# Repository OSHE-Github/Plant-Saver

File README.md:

# Plant-Saver
## Project Description
Many new gardeners or horticulturists struggle to create a proper environment for plant growth. The Plant-Saver aims to simplify the process and provide proper recommendations for the user. Housed in a convenient form factor, the device will analyze local conditions including temperature, soil moisture, humidity, and lighting. This data is utilized to provide recommendations for compatible species or for improving the care of a specific nearby plant. A simple local UI and accompanying web application ensures this information can be accessed efficiently in an easily digestible format. Environmental data is displayed along with an indication of how it compares to ideal conditions. Displaying the raw data readings while expressing recommended changes in simple terms allows the user to have a better understanding of their plant’s environment and how to alter it for improved growth.

*Main product image*

## Repository Structure
Project information/resources from semester 1 can be found in the folder Plant_Saver_Spring_2025. The newest iteration of the project from semester 2 is located in Plant_Saver_Fall_2026. This includes the following files/directories:
1. `Code`: Contains the arduino project used to program the Plant-Saver.
2. `JHA`: A job hazard analysis performed for the project.
3. `Plant_Saver_Kicad`: The KiCad project used to design the Plant-Saver’s PCB. This is the original version of the electrical design kept for posterity.
4. `Plant_Saver_Kicad_V2`: A KiCad project to which updates are being made to rectify the main issues found in testing of the original electrical design.
5. `Plant_Saver_Onshape`: Contains two STL files needed for printing the housing’s main body and back plate.
6. `Symbols_Footprints`: Symbol and footprint library storage for KiCad projects, separated from either project to be used globally.
7. `EmptyPlantSaverFs`: A zipped version of the Plant-Saver’s filesystem, “zeroed” out to its uninitialized form.
8. `plantSaverParser`: A python script used for pulling data using permapeople’s API and converting it into the database used by the Plant-Saver.

## Semester 1 in Brief
This project is the continuation of a prototyping phase performed in the previous semester (Fall 2025). The goal of that phase was to develop a functional breadboard version of the electronics, primarily for software development and testing purposes. The methodology of that prototype was very similar, but it was functionally limited so as to allow testing in a limited scope. Instead of a database with thousands of plants, a set of 10 were randomly chosen to be able to quickly optimize the formatting. An LTR390 was used in place of solar cells, which was a simpler sensing method but lacked the ability to detect the direction of incoming light and did not allow solar energy to be captured for powering the device. Battery charging was also not included in this prototype. Through developing and testing the device in this rudimentary state, its utility and feasibility were verified and a foundation for the Plant-Saver’s current software and database was developed.

# Methodology in Brief
## General Design overview
Building on the previous semester’s progress, the primary development goals were to:
1. Condense the form factor so as to be reasonably well-suited  for potted plant use and seal the device electronics to resist expected environmental conditions.
2. Expand the database to include all usable plants within the permapeople database.
3. Develop the existing UI to provide better recommendation, display, and search functions.
4. Move the majority of the device electronics to a single PCB to optimize space usage.
5. Integrate the new solar measurement method and battery charging into the device.

These goals were largely met in the current iteration of the project, although there is still room for improvement. Device electronics were condensed down to a single primary board with the DHT20, capacitive soil sensor, display, and other interface elements being connected via cables due to the need for flexible positioning. A 3D-printed enclosure was designed and produced out of PETG filament to house these electronics. This housing is compact, fitting easily into medium to large pots, and features dedicated ports for all externally accessible components which are sealed to prevent water ingress. The UI was expanded and now includes a local OLED display and remotely accessible web interface.

## General Program Execution

*High-Level operational flowchart of the Plant-Saver's software*

The normal operational loop that the Plant-Saver undergoes is as follows:
1. The ESP32 is woken by its RTC clock after the sampling period completes, or by a press of the select button.
2. Peripherals are powered on and initialized. This includes the display and all sensors.
3. The  header, parameters file, and active plant (if it exists) are pulled from the micro SD card.
4. Depending on the wake source, the device moves into one of two modes.
 - If the wake source was the select button, the device is moved into display mode. The watchdog timer is started and is reset every time an input is detected. Average readings are checked against a set of threshold values and recommendations are made to the user. After the watchdog timer completes, the device moves into shutdown mode.
 - If the wake source is the timer, the device moves into sensing mode. All sensor readings are taken and stored, the average readings are updated, and if there are enough readings new recommendations are generated.
5. The active plant is pushed back to the micro SD, temporary files are removed, peripheral power is removed, and the ESP32 is put back into deep sleep.

The broad structure of the program is designed around a state machine with individual functions for handling each state. Data is segmented into classes with self-contained methods for management. The main purpose of this is to keep the design as modular as possible such that it can be easily reconfigured.

If at any point during this sequence an error is detected, the error is displayed to the user by the local OLED display (if possible) and the indicator LED by a sequence of flashes. Errors that can be resolved without restarting are checked periodically, and if the source of the error is cleared the device restarts its initialization sequence.

## Sensing
The device utilizes four sensor types: photovoltaic cells, a combined temperature and humidity sensor, and a capacitive soil moisture sensor. The temperature and humidity sensor (DHT20) communicates with the ESP32 over I2C to deliver readings for both values. The capacitive moisture sensor is read directly from one of the microcontroller’s ADC pins. All four solar cells are measured by scaling their open-circuit voltage with a resistor divider network to a 0-3.3V range, the output of which is fed into a voltage-follower op-amp configuration and read by four separate ADC pins. All measurement devices are powered via a peripheral power bus which is only enabled when ESP32 is awake to save power. 

Each time the device wakes from deep sleep via the RTC timer, one measurement is taken from each device (solar panels are measured individually). Each JSON file for storing sensor readings is temporarily pulled into memory one-by-one so that the new reading can be added and the average readings updated. These files operate as rolling buffers where new readings replace the oldest data once the maximum number of readings is reached (default is 48). If a new plant is selected, these files are cleared immediately but the average readings for each environmental variable are held until the next sensor reading is taken.

The main variance in the sensing methodology from the previous semester’s prototype is in the use of solar cells to measure irradiance. Previously, the LTR390 was used for this purpose, but multiple factors led to this being swapped out. The form factor of the sensor meant it would be nearly impossible to hand-solder, and existing breakout boards would have been challenging to expose properly to ambient light. Other methods such as photoresistors were considered, but solar cells were chosen due to the fact that they allow for light energy to also be used for powering the device, making it more suitable for longer-term use.

# Bill of Materials
| # | Component | Qty | Total Cost | Link |
| - | --------- | --- | ---------- | ---- |
| 1 | 3.7V LiPo battery | 1 | $9.99 | [Makerfocus 3.7V 2000mAh](https://www.amazon.com/MakerFocus-Rechargeable-Protection-Insulated-Development/dp/B0DTHG757X?th=1) |
| 2 | 0.1 uF ceramic SMD capacitor | 5 | $0.6 | [C1206C104K5RACTU](https://www.digikey.com/en/products/detail/kemet/C1206C104K5RACTU/411248) |
| 3 | 10 uF ceramic SMD capacitor | 4 | $0.32 | [CL31A106KBHNNNE](https://www.digikey.com/en/products/detail/samsung-electro-mechanics/CL31A106KBHNNNE/3888534) |
| 4 | 1 uF ceramic SMD capacitor | 5 | $0.335 | [CL31B105KAHNNNE](https://www.digikey.com/en/products/detail/samsung-electro-mechanics/CL31B105KAHNNNE/3886755) |
| 5 | 1 nF ceramic SMD capacitor | 1 | $0.11 | [CL31B102KBCNNNC](https://www.digikey.com/en/products/detail/samsung-electro-mechanics/CL31B102KBCNNNC/3886708) |
| 6 | 4.7 uF ceramic SMD capacitor | 1 | $0.16 | [CL31B475KAHNNNE](https://www.digikey.com/en/products/detail/samsung-electro-mechanics/CL31B475KAHNNNE/3886713) |
| 7 | Red through-hole LED | 1 | $0.14 | [LTL-4224](https://www.digikey.com/en/products/detail/liteon/LTL-4224/217584) |
| 8 | Yellow through-hole LED | 1 | $0.16 | [LTL-4253](https://www.digikey.com/en/products/detail/liteon/LTL-4253/214719) | 
| 9 | Green through-hole LED | 1 | $0.14 | [LTL-4231](https://www.digikey.com/en/products/detail/liteon/LTL-4231/670004) |
| 10 | 10-Pin male header, 2.54mm | 2 | $0.48 | [SBH11-PBPC-D05-ST-BK](https://www.digikey.com/en/products/detail/sullins-connector-solutions/SBH11-PBPC-D05-ST-BK/1990062) |
| 11 | 4-Pin JST SH header, 1.00mm | 1 | $0.5 | [SM04B-SRSS-TB](https://www.digikey.com/en/products/detail/jst-sales-america-inc/SM04B-SRSS-TB/926710) |
| 12 | 3-pin JST PH header, 2.00mm | 1 | $0.12 | [S3B-PH-K-S](https://www.digikey.com/en/products/detail/jst-sales-america-inc/S3B-PH-K-S/926627) |
| 13 | 6-pin USB-C port | 1 | $2.5 | [54-00284](https://www.digikey.com/en/products/detail/tensility-international-corp/54-00284/15667380) |
| 14 | 1.25mm Micro-JST style male port | 1 | $0.3 | [530470260](https://www.digikey.com/en/products/detail/molex/0530470260/15622895) | 
| 15 | Micro-SD port | 1 | $1.83 | [DM3D-SF](https://www.digikey.com/en/products/detail/hirose-electric-co-ltd/DM3D-SF/1786510) | 
| 16 | PMOS | 10 | $3.55 | [G09P02L](https://www.digikey.com/en/products/detail/goford-semiconductor/G09P02L/16533523) |
| 17 | PMOS | 2  | $2.380 | [ISP12DP06NMXTSA1](https://www.digikey.com/en/products/detail/infineon-technologies/ISP12DP06NMXTSA1/10058802) |
| 18 | 10k SMD resistor | 11 | $0.132 | [RC1206FR-0710KL](https://www.digikey.com/en/products/detail/yageo/RC1206FR-0710KL/728483) |
| 19 | 100k SMD resistor | 3 | $0.033 | [RC1206FR-07100KL](https://www.digikey.com/en/products/detail/yageo/RC1206FR-07100KL/728492) |
| 20 | 150k SMD resistor | 2 | $0.032 | [RC1206FR-07150KL](https://www.digikey.com/en/products/detail/yageo/RC1206FR-07150KL/728562) |
| 21 | 5.1k SMD resistor | 2 | $0.026 | [RC1206FR-075K1L](https://www.digikey.com/en/products/detail/yageo/RC1206FR-075K1L/728947) |
| 22 | 200k SMD resistor | 4 | $0.04 | [RC1206FR-07200KL](https://www.digikey.com/en/products/detail/yageo/RC1206FR-07200KL/728676) |
| 23 | 10k NTC thermistor | 2 | $1.70 | [NTCLE317E4103SBA](https://www.digikey.com/en/products/detail/vishay-dale/NTCLE317E4103SBA/12331368) |
| 24 | 1k SMD resistor | 1 | $0.1 | [MFR-25FRF52-1K](https://www.digikey.com/en/products/detail/yageo/MFR-25FRF52-1K/14891) |
| 25 | 1k through-hole resistor | 1 | $0.1 | [MFR-25FRF52-1K](https://www.digikey.com/en/products/detail/yageo/MFR-25FRF52-1K/14891) |
| 26 | 5.6k through-hole resistor | 1 | $0.1 | [MFR50SFTE52-5K6](https://www.digikey.com/en/products/detail/yageo/MFR50SFTE52-5K6/9151627) |
| 27 |20k through-hole resistor | 1 | $0.1 | [MFR-25FBF52-20K](https://www.digikey.com/en/products/detail/yageo/MFR-25FBF52-20K/13276) |
| 28 | 220 through-hole resistor | 3 | $0.3 | [CFR-25JR-52-220R](https://www.digikey.com/en/products/detail/yageo/CFR-25JR-52-220R/11958) |
| 29 | 205k through-hole resistor | 5 | $0.195 | [MFR-25FBF52-205K](https://www.digikey.com/en/products/detail/yageo/MFR-25FBF52-205K/13549) |
| 30 | 301k through-hole resistor | 5 | $0.195 | [MFR-25FRF52-301K](https://www.digikey.com/en/products/detail/yageo/MFR-25FRF52-301K/15121) |
| 31 | 3.6k through-hole resistor | 1 | $0.1 | [MFR-25FTE52-3K6](https://www.digikey.com/en/products/detail/yageo/MFR-25FTE52-3K6/9140152) |
| 32 | 22.1k through-hole resistor | 1 | $0.1 | [MFR-25FTE52-3K6](https://www.digikey.com/en/products/detail/yageo/MFR-25FTE52-3K6/9140152) |
| 33 | 71.5k through-hole resistor | 1 | $0.1 | [MFR-25FBF52-71K5](https://www.digikey.com/en/products/detail/yageo/MFR-25FBF52-71K5/13444) |
| 34 | 402k through-hole resistor | 1 | $0.1 | [MFR-25FBF52-402K](https://www.digikey.com/en/products/detail/yageo/MFR-25FBF52-402K/13620) |
| 35 | ~1" solar cell | 4 | $23.52 | [KXOB061K08F-TR](https://www.digikey.com/en/products/detail/anysolar-ltd/KXOB061K08F-TR/13999192) |
| 36 | 6mm pushbutton switch | 2 | $0.48 | [SKHHAJA010](https://www.digikey.com/en/products/detail/alps-alpine/SKHHAJA010/19529121) |
| 37 | SPDT slide switch | 1 | $7.16 | [1101M2S3AQE2](https://www.digikey.com/en/products/detail/c-k/1101M2S3AQE2/67052) |
| 38 | Thermal switch/thermostat | 1 | $1.24 | [SA72SB0](https://www.digikey.com/en/products/detail/bourns-inc/SA72SB0/6830067) |
| 39 | Tall pushbutton switch | 4 | $0.68 | [3-1825910-5](https://www.digikey.com/en/products/detail/te-connectivity-alcoswitch-switches/3-1825910-5/1632530) |
| 40 | Schottky diode | 6 | $4.92 | [CDBA140SL-HF](https://www.digikey.com/en/products/detail/comchip-technology/CDBA140SL-HF/3308122) |
| 41 | ESP32 module | 1 | $5.71 | [ESP32-WROOM-32E-N16](https://www.digikey.com/en/products/detail/espressif-systems/ESP32-WROOM-32E-N16/11613144) |
| 42 | DHT20 temp/humidity sensor | 1 | $4.5 | [5183](https://www.digikey.com/en/products/detail/adafruit-industries-llc/5183/15204087) |
| 43 | DW03C battery protection chip | 1 | $0.1 | [DW03C](https://www.digikey.com/en/products/detail/shenzhen-slkormicro-semicon-co-ltd/DW03C/28142983) |
| 44 | Programmable linear regulator | 1 | $1.89 | [LP38511TJ-ADJ/NOPB](https://www.digikey.com/en/products/detail/texas-instruments/LP38511TJ-ADJ-NOPB/2023099) |
| 45 | Battery charging chip | 2 | $2.48 | [MCP73833-CNI/UN](https://www.digikey.com/en/products/detail/microchip-technology/MCP73833-CNI-UN/1223169) |
| 46 | 4-Circuit op-amp | 1 | $0.8 | [MCP6234-E/P](https://www.digikey.com/en/products/detail/microchip-technology/MCP6234-E-P/857555) |
| 47 | 2-Circuit comparator | 1 | $0.62 | [MCP6547T-I/MS](https://www.digikey.com/en/products/detail/microchip-technology/MCP6547T-I-MS/458408) |
| 48 | 10-Pin IDC cable 2.54mm | 1 | $1.12 | [H3DDS-1006G](https://www.digikey.com/en/products/detail/assmann-wsw-components/H3DDS-1006G/1218627) |
| 49 | 3-Pin JST cable 2.00mm | 1 | $1.05 | [A03KR03KR26E152B](https://www.digikey.com/en/products/detail/jst-sales-america-inc/A03KR03KR26E152B/6708616) |
| 50 | 4-Pin JST SH connector | 1 | $0.95 | [4210](https://www.digikey.com/en/products/detail/adafruit-industries-llc/4210/10230021) |
| 51 | Capacitive soil moisture sensor | 1 | $5.67 | [3PCS capacitive soil moisture sensor](https://www.amazon.com/VKLSVAN-Capacitive-Corrosion-Resistant-Detection/dp/B0DQSCD5CV/ref=sr_1_8?crid=2T3W8GRPEPAZO&dib=eyJ2IjoiMSJ9.VDQmMTvA56NE3sh9LcnMjGEhAQiaewfNTo0PxVwCtq20CpiVuc_oL4U8zqIeN2SI6TsorswAe4DcuEpW3kwDSQAY8mm10fgVrGpoDDBsUGHwlLMTe_0tMgvywFzmPk4HuteChVSr-0URo3wA7EzUY787M0kiv-VemaUegofTH7UwfMTeryxjkYHyxM7BOS9Vw_Nq4K6onMX47QMQvUe-syFdiFBW1ohNYQjR-CtfuROxCKTlcSYXfY_iLdHu-LCjD08GmoRkG9fq-5Pi9IY9zhBk_CT5Y_BQhETmEpO4YTs.eDALyc1xMEA73WswnEQ_UNPWlAWnb9vSysE4Zj-Z4Gc&dib_tag=se&keywords=capacitive%2Bmoisture%2Bsensor&qid=1771442737&sprefix=capacitve%2Bmoisture%2Caps%2C156&sr=8-8&th=1) |
| 52 | 1.3" monochrome OLED display | 1 | $19.95 | [938](https://www.adafruit.com/product/938?srsltid=AfmBOopGujMlQ19b1HjKU9Gz_qpD8YPfFucayyibxzuMLd3uAxlGnX66) |
| 52 | Stripboard/perfboard |  |  |  |
| 53 | PETG filament |  |  |  |
| 54 | RTV silocne sealant |  |  |  |
| 55 | Kapton tape |  |  |  |
| 56 | M2 Screws |  |  |  |
| 52 | M2 nuts |  |  |  |

**Notes on Bill of Materials:**

All items listed are from the “V1” electrical design, constructed in the project’s second semester. With minor modifications this version is functional, but not all features were fully realized. Of particular note is item 40 on this list, the 6 Schottky diodes which are primarily used for reverse blocking, as this part did not function as expected in our testing and should not be used for this project. The current replacement candidate (untested as of yet) is the CRS10I30C from Toshiba Semiconductor, although this does have a different footprint. Also of note are items 12 and 49, which are a header and cable respectively meant for connection of the capacitive moisture sensor. The pitch of this cable’s connector is incorrect for mating with the headers on the sensors used in the Plant-Saver, and so requires modification to be used. These should be replaced with 2.54mm pitch XH or SH-style connectors, such as the 25SH-B-03-TR shrouded 3-pin header (and accompanying compatible cable).

# Tools used
| Component | Use | Link |
| --------- | --- | ---- |
| Soldering station | Populate PCB | [Hako 888](https://www.ifixit.com/products/soldering-station-hakko-fx888d-23by?lnid=CjwKCAjwwJzPBhBREiwAJfHRnct3H0tR7nU-cJzkjclwdoABVduTF6vOiET7RmJEt9MUSL2tfSOEwhoCr4MQAvD_BwE&utm_source=google&utm_medium=cpc&utm_campaign=21364903818&utm_term=&utm_content=&tw_source=google&tw_adid=&tw_campaign=21364903818&gad_source=1&gad_campaignid=21371193557&gbraid=0AAAAACuwhq5AtuEWQldLTa-Vttl-HQ26L&gclid=CjwKCAjwwJzPBhBREiwAJfHRnct3H0tR7nU-cJzkjclwdoABVduTF6vOiET7RmJEt9MUSL2tfSOEwhoCr4MQAvD_BwE) |
| Multimeter | Measure voltage and current for PCB validation | [Klein MM325](https://www.kleintools.com/catalog/multimeters/digital-multimeter-manual-ranging-600v-0) |
| Sealant | Adhesive to affix solar panels and UI stripboard | [Clear Silicone RTV Sealant](https://www.amazon.com/Permatex-80050-Silicone-Adhesive-Sealant/dp/B0002UEPVI/ref=sr_1_3?crid=300SS11OFUJAU&dib=eyJ2IjoiMSJ9.lMHOvPXrJL-erz2RLlp5h9Bj5Gugm79FTFMztWvVJAZTfAEDilmMbuq9QWJcelpgCGfmew0R9XLf_4lIiHwveiQKjniAkaROHKqgHcO30IK5zvZ4GxpMcoj4Q9GvhXKbrDnI2Mgf5uMaYyHFEYBsLIHCok_H4aZiN-ZhkOvPqln6VJJmi2BtlZE4frDc2ngy_OdBQsurh65VRnla6rk2yrjv2fKwx0wdvsTYFyyhU9I.N76MvPLgIPCmebUMwT9mRWcgPc7rcxGBiP9dn3Hc3-U&dib_tag=se&keywords=rtv+silicone+sealant+clear&qid=1776825413&sprefix=rtv+silicone+sealant+clea%2Caps%2C198&sr=8-3) |
| 3D printer | Create housing | [Prusa Core One](https://www.prusa3d.com/product/prusa-core-one/) |
| KiCad | Create PCB and schematic | [KiCad Download](https://www.kicad.org/download/) |
| Onshape | Create housing model | [Onshape](https://www.onshape.com/en/) |
| Arduino IDE | Develop and upload program | [IDE Download](https://www.arduino.cc/en/software/) |
| FTDI breakout | Convert USB data to UART for programming the microcontroller | [USB to UART Bridge](https://www.amazon.com/ALMOCN-Converter-Adapter-Breakout-Compatible/dp/B0FWBLW58D?crid=36AOETKEREG2C&dib=eyJ2IjoiMSJ9.9N_ITnsSrm6AsLlIA8zdMjdRkmCJCPpsct6Gm5-LhFhtt0it2NA1_HJ54N89o4667oOHAKTTrQCjL3_qIoLIPlhIC-bsue3BNtu9NKNOpOQQ6KNpf-FXgDVGdgKhCi-p--L0JEZXr-55ZzsA2iLMd6bad30lvakcnc1YJtWxYh8wqVRl5JQ56RjrKZE9LgGR93lqQOooDiW9QdIABYsWZWFmi3kWKTqgauo1wbiVdig.JjUBWDxI5ogOyk18AHwMYy6pHYDV_K6hNzl7mmBij-w&dib_tag=se&keywords=ftdi+esp32&qid=1776436845&sprefix=ftdi+esp3%2Caps%2C452&sr=8-3) |

# Assembly instructions
## PCB Assembly
The PCB can be assembled in two ways. The most straight forward assembly method is to begin with complex components that require more finesse. This would be the ESP32 Processor and U15/U13 (the battery charge ICs). Almost all components present in the BOM will be used to populate the main PCB pictured below in figure XXX. Hand soldering is acceptable for all components, but the assembly process can be greatly sped up with the use of reflow ovens for the above-mentioned components and other ICs. If the assembler wants to test each individual circuit during assembly to verify operation, the process will look a little different.

*Plant-Saver PCB design*

**USB Power Path:**

When assembling to test each sub circuit it is still acceptable to begin with the fine pitch components. Ensure SW2 is not attached to the PCB to prevent any incorrect voltages from affecting the ESP32. Beginning with the charge and power circuits, the USB module, R7, and R8 can be added to the circuit for usb power. The linear regulator circuit will be added next to connect the USB input to the microcontroller. For this, add diodes U9 and U11 then R16-18, C6-8, and U12. This creates a path to ensure the microcontroller will see its expected input voltage. To validate, observe the USB1 test point to check for 5V and the Bus1 test point for 3.3V.

**USB Battery Charge:**

The USB charge circuit will also need to be installed, this consists of C14, C15, R38, and the previously added U15. This would be a good time to add in the charge logic transistor paths. Using 6 of G09P02L, solder Q5-10 and resistors R13 and R14. Finally, add R15, SW4, C5, and U10. These are safety measures added close to the battery for protection. This will complete the path from the USB input to both the battery pins and the voltage regulator. Ensure the BAT1 test point is receiving proper voltage for the battery being used, this should be around 3.7-4.2 volts in this application. In our testing, the schottky diodes used were not sufficient for this project and had to be replaced. This will require finding independent diodes of similar footprint, modifying the PCB slightly to utilize a diode of a different footprint, or other creative solutions.

**Solar UVLO & Charge:**

With the power path complete, the next circuit to test is the Solar UVLO and charge. During testing use wires to simulate solar voltage inputs, it is much easier than testing with the panels attached. The UVLO circuit is relatively simple to integrate. Add the comparator IC to U16, R39-45, and C16. These components make up the comparator circuit, but will need Q11 and Q12 to pass the input voltage through to the power circuit. Ensure the voltage seen at the drain pin of Q12 is only high when between the input ranges of 4.5 to 5.3 V. Once this circuit is validated, add Q3, Q4, R9, and R10 to connect the UVLO to the solar charge circuit. Solar charge is very simple to integrate, just add C11, C12, and R26 to their positions near U13 to complete. With this, the power circuit is complete.

**Solar Voltage Measurement:**

A final complex circuit to validate is the solar measurement system. This steps down the solar input voltage to be read and used by the microcontroller. All this system needs is the U14 op amp, R30-37, and C13. This system uses 4 op amps to adjust each solar input source. Once this circuit is added, test to see the voltage at VSolar1 is approximately equal to the voltage at Sol1 * 0.6. With this, all of the complex circuits are validated.  The rest of the Plant-Saver PCB is able to be assembled using hand soldering techniques, with a few exceptions detailed below.

**Assembly Warnings:**

The DHT20 is a temperature sensitive device that can be impacted by soldering heat. The adafruit datasheet suggests no more than 5 seconds of contact @ 300 °C. This was avoided by using wire extensions and positioning the sensor towards a vent on the housing. Additionally, J2 is a 10 pin connector to connect a UI board to the main pcb. This board will need to be assembled on a stripboard or a user made PCB. Ensure the positioning of the buttons and LEDs will fit inside the UI board housing by adjusting their positioning in a 3D modeling program. The pinout is pictured below in the below table. Additionally, J7 and J6 are utilized for chip programming purposes only. They do not need to be physically attached to the PCB at all times, only when updating the device’s code.

| Pin | Function |
| --- | -------- |
| 1 | 3.3V | 
| 2 | Charge in progress LED (yellow) |
| 3 | Charge complete LED (green) | 
| 4 | Error LED (red) |
| 5 | Up button | 
| 6 | Down button |
| 7 | Change screen button |
| 8 | Select button |
| 9 | Ground |
| 10 | Not used |

## Code Upload/configuration
To upload this project’s code to the ESP32, start by downloading and installing the Arduino IDE if you have not already. Instructions for doing so can be found here: https://support.arduino.cc/hc/en-us/articles/360019833020-Download-and-install-Arduino-IDE
Additionally, you will need to download the project code and filesystem. These can be found at the project’s github repository [1] or OSF page [2]. In order to communicate with the ESP32 you will need to first install the CP210x USB to UART bridge driver [3]. Following that, open the Arduino IDE and navigate to “File” > “Preferences” > “Settings”. Add the following link to the “Additional boards manager URLS” field: https://espressif.github.io/arduino-esp32/package_esp32_index.json.

*Arduino IDE additional boards manager URLs*

Click “OK” to save this change, then click “File” > “Open…” and select the main project file (Plant_Saver_Spring_2026.ino) in the project folder downloaded from the GitHub repository. As long as the other project files (PlantSaverClasses.h, plantSaverClasses.cpp, plantServer.h, plantServer.cpp) are also in the same folder as this file, they should also be opened automatically. At the top of each file are a list of Macros used within that file. These are names which the compiler automatically substitutes with the associated value when building the project. They are convenient to prevent having to change constant values in multiple locations, since updating the definition will alter all uses of the same macro. In the main file, the most pertinent value is DISPLAY_TIMEOUT_M, which determines the time in minutes before the device returns to sleep mode when no activity is detected. There is also a constant value, samplingPeriodM, which sets the time between samples in minutes. Additionally, all pin definitions for the project are set here should you need to alter them. If so, keep in mind that certain pins on the ESP32 have limited functionality. A good reference for determining which pins to use can be found here: https://lastminuteengineers.com/esp32-pinout-reference/. 

The PlantSaverClasses.h file also contains a number of macros which are less likely to need editing, but may be helpful in implementing simple changes to this project such as storing more sensor readings. It is recommended that you only edit these if you are confident in your ability to understand and debug C/C++ code, as the functionality of this project has not been tested with alternate values for the vast majority of these macros.

There is a line of five holes near the power switch intended for vertical header pins. The order of these pins matches that of common USB to Serial converters, although it may be more convenient to connect these together using wires rather than plugging the converter directly into the board.

*USB to UART converter connection points*

The labels on these pins indicate the pins on the converter that should be connected to them. The converter Tx should connect to the pin labeled Tx, Rx to Rx, and Ground to GND. These are the only three pins that need to be connected. After connecting the converter to the board and connecting it to your computer via a USB or USB-C cable, provide power to the microcontroller. To put the controller into programming mode:
1. Press and hold the boot button
2. Press and release the reset button
3. Release the boot button

To upload code to the ESP32, first open the board selection dropdown located to the right of the “debug” button (“Select other board and port”). For the board, select “ESP32 Dev Module”. The Arduino IDE should be able to detect that a device is plugged into one of your computer’s ports automatically, in which case it will show up under the “Ports” tab, and can be selected to use. Otherwise, to double check that your device has been recognized and the drivers are properly installed open the Device Manager application and expand the Ports (COM & LPT) section. If this section is not shown or there is not a device listed under the connected port, it is likely that either the device has not been recognized, the drivers are not installed properly, or some other issue is hindering the connection process (such as a faulty cable). Next to the name of this device will be the word “COM#”, where # is the port number that it is plugged into. This should be the same as the port selected in the Arduino IDE.

*Arduino IDE board selection dropdown*

Finally, to upload code to the board click the “Upload” button located at the top left of the IDE (a right-facing arrow).

# Characterization Data
## Sensor Calibration
Each sensor on the Plant-Saver should be calibrated/tested, although some do not require it for basic operation. Should you desire to calibrate your own Plant-Saver with values other than the defaults, the methods we used are listed below. A breadboard test setup will be easiest to use for this process, but the Plant-Saver board can be used by reprogramming the microcontroller for each test if needed.

**Soil Moisture:**

1. Spread a sample of potting soil over a wide, flat, oven-safe container such as a baking tray lined with foil. 
2. Place the sample in an oven at approximately 200 degrees Fahrenheit until little to no moisture remains. This took about 6-8 hours in our testing, but the best way to be certain is to weigh the sample periodically. When the weight stops changing it is mostly dry.
3. Find a vessel such as a drinking glass or tin can. Using a kitchen scale, tare the empty container and record the weight. Then transfer the sample and take the weight again, subtracting the empty value to find the total dry sample weight. Record this value.
4. Insert the capacitive sensor into the soil (do  not go past the white line). Wait until the readings stabilize and record the steady-state value.
5. Add approximately 10 percent of the dry soil weight in water to the sample. Mix thoroughly. If the water is not dispersed fully, wait until it is relatively well distributed.
6. Repeat steps 4 and 5. We collected up to 170% total added weight in data, as at this point the water began to pool and become poorly distributed, invalidating results following this level of saturation.
7. Perform a linear regression using a tool such as Wolfram|Alpha or Desmos. ADC readings are the independent variable (X), and fraction of dry weight (out of 1, ex: 110% = 1.1) are the dependent variable (Y). Record the coefficients (m and b).

**Light:**

Calibrating the solar cells is a twofold process. To translate ADC readings to solar cell voltages, perform the following steps after populating the PCB but before adding the solar cells:

1. Connect an adjustable voltage source such as a bench power supply to any solar cell connection point with the voltage set to 0V.
2. Power the PCB using either the battery or by injecting a constant voltage source into the supply rails.
3. Record the ADC reading on the corresponding microcontroller pin.
4. Increase the voltage by 0.1 V.
5. Repeat 3 and 4 up to ~5.3 V.
6. Perform a linear regression using a tool such as Wolfram|Alpha or Desmos. ADC readings are the independent variable (X), input voltages are the dependent variable (Y). Record the coefficients (m and b).
	
To translate solar voltages into irradiance values, perform the following steps:
	
1. Using tape or some other method, mark a point on a flat workspace.
2. Place a light source such as a flashlight at a constant height above this point. We used clamps and the side of a desk for this, but any solution which allows the light to be easily adjusted in height will work. 
3. Place a light sensor such as the LTR390 underneath the light source at the marked point and measure the light read.
4. Place a solar cell at the same point and measure the voltage across its positive and negative terminals.
5. Repeat steps 3 and 4 at various heights. Try to get a broad range of light readings, from several hundred Lux up to several tens of thousands.
6. Perform an exponential regression (y =a*c^(x)) using a tool such as Wolfram|Alpha or Desmos. Voltage readings are the independent variable (X), and light readings (in Lux) are the dependent variable (Y). Record the coefficients (a and c).

**Temperature:**

1. Apply a low-intensity heat source to the DHT20.
2. Wait until the reported temperature stabilizes, then record the value (in degrees Celsius).
3. Measure the temperature of the DHT20 using another sensor such as an IR thermometer or thermocouple and record the value (in degrees Celsius).
4. Repeat 1-3, slowly increasing the temperature applied. 10 data points over a span of 20 or so degrees celsius is sufficient. 5. 5. Take care not to apply too much heat, as this may damage the sensor.
6. Perform a linear regression using a tool such as Wolfram|Alpha or Desmos. DHT20 temperature readings are the independent variable (X), and actual temperature readings are the dependent variable (Y). Record the coefficients (m and b).

**Humidity:**

1. Fill a small container such as a bottle cap with a mixture of approximately 75% salt, 25% water. When mixed,  this should form a slurry with the consistency of wet sand.
2. Seal this container in a plastic bag with the DHT20 and a separate hygrometer in such a way that allows measurements to be taken from the sensor while still sealed in the bag (such as attaching leads that extend outside the bag). Take care not to let any water spill onto the DHT20, and do not press the air out of the bag before sealing it.
3. Leave the bag overnight (8-10 hours) to allow the humidity inside to settle
4. Take a humidity reading from the DHT20 and the hygrometer, record both values, and remove them from the bag. The actual humidity value should be around 75%.
5. Wait a few minutes for both devices to readjust to the room humidity, and then record the humidity read by both.
6. Perform a linear regression using a tool such as Wolfram|Alpha or Desmos with the two points of data collected. DHT20 humidity readings are the independent variable (X), and actual humidity readings are the dependent variable (Y). Record the coefficients (m and b).

When each sensor has been tested, open the “params” file within the plant-saver’s root directory on the Micro-SD. The “empty” filesystem includes the default values for calibrating each sensor collected by our enterprise team, which can now be replaced. All parameters correspond to coefficients of polynomials of form y = m*x + b, save for the light parameters “a” and “c”. These correspond to the two values found in the second step of the light calibration. 

## Battery Draw / Power Consumption Characterization
The target for the Plant-Saver’s single-charge battery life was set at 7 days of normal use. After determining the discharge curve of the batteries used, the device was tested for a cumulative period of 24 hours without charging the battery. Extrapolating this test data using the discharge curve led to a maximum life of 9 days, with 7-8 being more likely. The methods used in our testing are as follows:
1. Connect the battery to a constant impedance. We tested with 6 parallel 100 Ohm resistors, which in combination created a total resistance of 16.6 Ohms. This led to a draw of 190-240 mA over the course of the test, which allowed the battery to be discharged over the course of 8.5 hours without putting excessive load on it.
2. Take current and voltage readings from the battery roughly every hour. The current readings can be used to determine the capacity usage of the battery at the time of each voltage reading.
3. Plot the voltage-capacity data to get an approximate discharge curve. A quartic regression works well to approximate this data, which is fairly consistent with standard LiPo discharge curves.
4. Find the low-voltage cutoff point of the device on this graph, which is determined by the dropout of the linear regulator (0.26 V + 3.3 V = 3.56 V). The point at which the curve crosses this point is the total capacity available to the device (1469 mAh).
5. Recharge the battery, then use it to power the Plant-Saver for 24 hours. We took voltage measurements periodically for validation, but this is not strictly necessary. 
6. Measure the voltage of the battery after the 24-hour period. Then find where this voltage intersects the discharge curve. This is the capacity usage after 1 day (154 mAh). The electronics on the Plant-Saver are relatively consistent in their current usage, so this value can be used to extrapolate capacity usage for any period simply by multiplying. After 7 days, the expected battery voltage would be 3.72 V, which intersects the curve at 1078 mAh.

*Plant-Saver power consumption characteristics*

## Housing
When creating an enclosure for the PCB, it was necessary to ensure that each sensor could obtain accurate readings while maintaining environmental resistance and a form factor suitable for potted plant use. As a baseline design, a structure resembling a birdhouse with a hip roof was developed to balance functionality and aesthetics. The four angled sides of the roof allow for straightforward integration of inlays for solar panels, enabling the collection of sunlight data from multiple directions.

The DHT20 temperature sensor is housed in a pocket located toward the front of the enclosure, positioned between the user interface (UI) screen and buttons. To ensure accurate environmental readings while maintaining protection, a grated opening was incorporated, allowing airflow without exposing the sensor to damage. The moisture sensor, which must be inserted into soil for proper operation, is accommodated by a slit at the bottom of the enclosure. A supporting ledge is included to secure the sensor by the rear of its female connector.

The OLED display is mounted to the front of the enclosure using bolts, with an additional outcrop to accommodate wiring connections. The buttons and LEDs are soldered onto a stripboard, which is then affixed to a designated inlay, with corresponding openings for user interaction and visibility.

To allow access to the PCB, a removable back panel is implemented. The PCB is secured to this panel using two screws, and the assembled panel is then fastened to the main housing once all necessary connections are made.

For accessibility and ease of manufacturing, the enclosure is designed for 3D printing. The model can be produced in two parts with minimal error. PETG is recommended as the printing material due to its durability and improved environmental resistance.

## User Interface / Web App

The device makes use of two different user interfaces, a physical one, and a web app. The physical interface is operated using the buttons on the front of the device, and the web interface can be accessed by connecting to the device’s access point using standard WIFI. Both of these interfaces are synced together, and start up automatically when the device is powered on entering sleep mode upon 60 seconds of inactivity for power saving purposes. The physical interface is made up of four independent push buttons and an OLED display. Each of these buttons serves a different function: one to change screens, one to ‘scroll’ up, one to ‘scroll’ down, and a ‘select’ button, which also serves as the ‘wakeup’ button for when the device is in sleep mode. The physical interface itself consists of three primary screens: 
- A “main menu” to display sensor data averages and recommendations. Recommendations are provided in a graphical form. For each data type, a set of two tall vertical lines represents the minimum and maximum measurable values. A set of two shorter lines represents the recommended thresholds for the selected plant, and a flower-shaped marker represents the average readings. If this marker is outside the recommended thresholds, an arrow will be present showing the desired direction. Pressing the “select” (left) button focuses on this menu, allowing the up/down buttons to be used for highlighting one of the four data types. Pressing select again moves to a display showing more information on the highlighted data type, including the average value, recommendation thresholds, units, and additionally the primary direction if the value selected is sunlight.
- A “info menu” to display additional information on the plant such as scientific name and environmental preferences in text form. 
- A “search menu” to lookup plants from the database. Pressing select focuses on this display, allowing the up/down buttons to be used for alphabetically scrolling the highlighted letter in the displayed five-character query. Pressing the change screen button with focus on this menu changes the highlighted character. Pressing and holding the change screen button exits focus. Pressing select while focused on this menu initiates a search of the database for the query, moving to a scrollable list of plants with similar names. 

Additionally, there is a recommendation request screen which is only available if the device has enough data to recommend a suitable plant. Pressing select on this menu brings up a scrollable list of candidate plants to choose from. Pressing select on either scrollable menu (recommendation or post-search) sets the highlighted plant as the active plant, clearing out existing sensor data.

The web interface is a locally hosted website, accessible through the device’s access point as mentioned earlier. The default SSID and password for the device are set as ‘Plant-Saver’ and ‘plants123’ respectively, both of which could be altered if desired. The website itself displays much of the same information as the physical interface, the main difference found in the comparison between a plant’s environmental requirements and the current sensor readings. The web interface displays both the requirements and the sensor readings interpreted in accordance with the calibration of our sensors. This allows for a more specific idea of the relation between the requirements and the actual environment. The website additionally displays the same list of recommended plants as the physical interface. In search of a more efficient plant selection method the web interface implements a ‘search by name’ function that makes use of a prefix-autocomplete feature to ease the selection process. This search box allows the user to type the name of the plant they are interested in. As they type, the device sorts through the database based on their current input and displays plants with similar prefixes in a list below the search box. This was done in an attempt to remove the headache of determining if a plant exists on the device’s database, as well as smoothen the overall process of changing selected plants. Finally, in the interest of user convenience, as mentioned above the physical and web interfaces are synchronized. This means that selecting a plant on one will display the selection on both, ensuring consistent, accurate name and requirement displays across both interfaces. 

## Plant Database
The Plant-Saver uses four pieces of data to determine plant health, with recommended values for three of these in the form of USDA hardiness zone ,water requirements, and light requirements being provided by permapeople’s database. The plant ID, common name, and scientific name are also sourced from this database. The plant parsing script ensures that the data that is taken from permapeople can be used by the on-board data processing. It does this by first calling permapeople's API until all available plants have been received, as each call returns roughly 100 plants worth of data. After all of the data is obtained, each plant entry is combed through to find all of the plants that have the requisite information to be used with the Plant-Saver. While the plants are being searched through, all of the data provided by permapeople that isn’t used in our analysis is removed to save on storage space on-board the Plant-Saver. Additionally, when removing extraneous data, all of the text-based data is converted to enumerated numerical representations that correlate to each of the options for hardiness zone, light requirement, and water requirement for simpler use onboard the Plant-Saver. After each plant is determined to have adequate data, each of the plants that do not have adequate data are removed from the list. After the unwanted plants have been culled, the remaining plants are saved to a JSON file that is ready to be manually loaded onto the device's SD card.

# Acknowledgements
- Permapeople database at permapeople.org
- Dr. Shane Oberloier for his advisorship
- Michigan Technological University for the facilities and funding
- All OSHE members for their direct and indirect support

# References
[1] OSHE, “GitHub - OSHE-Github/Plant-Saver,” GitHub, 2025. https://github.com/OSHE-Github/Plant-Saver (accessed Dec. 05, 2025).

[2] Plant-Saver, “OSF,” Osf.io, 2025. https://osf.io/kzrm2/overview (accessed Dec. 05, 2025).

[3] “Silicon Labs,” Silabs.com, 2025. https://www.silabs.com/software-and-tools/usb-to-uart-bridge-vcp-drivers?tab=downloads

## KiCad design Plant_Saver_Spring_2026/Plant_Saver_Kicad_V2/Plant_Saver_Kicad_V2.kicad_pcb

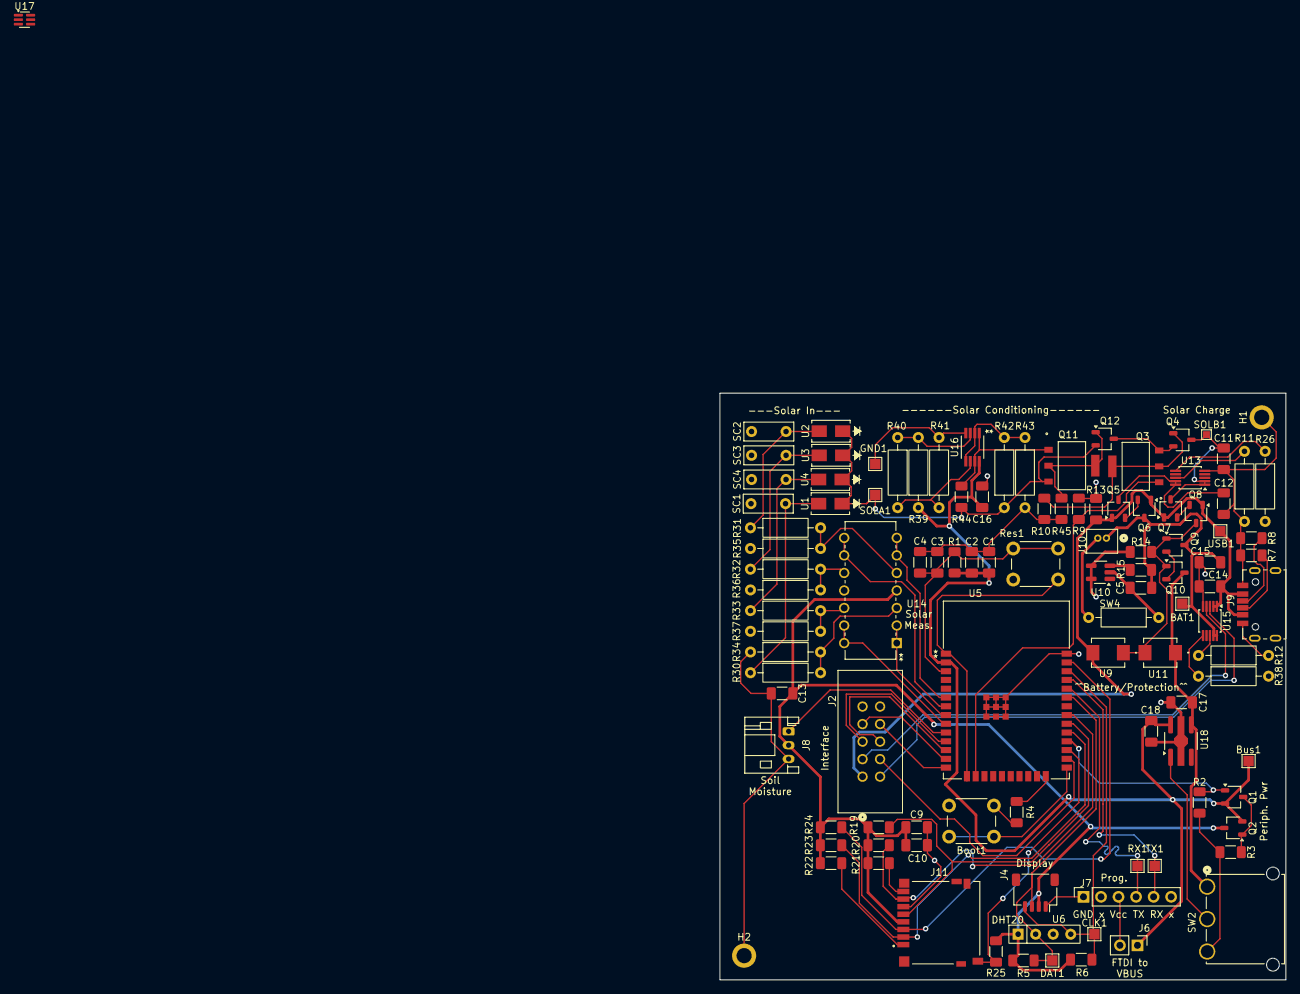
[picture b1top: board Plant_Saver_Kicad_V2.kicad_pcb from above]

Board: 2 copper layers, 82.0 x 85.0 mm, 109 parts (0 on the bottom side), 68 nets.

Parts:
BAT1: TestPoint; TestPoint_Pad_1.5x1.5mm
Boot1: Boot; SW_PUSH_6mm
Bus1: TestPoint; TestPoint_Pad_1.5x1.5mm
C1, C4, C10, C13, C16: 0.1uF; C_1206_3216Metric_Pad1.33x1.80mm_HandSolder
C2, C9: 10uF; C_1206_3216Metric_Pad1.33x1.80mm_HandSolder
C3, C5, C11, C12, C14, C17, C18: 1uF; C_1206_3216Metric_Pad1.33x1.80mm_HandSolder
C15: 4.7uF; C_1206_3216Metric_Pad1.33x1.80mm_HandSolder
CLK1: TestPoint; TestPoint_Pad_1.5x1.5mm
DAT1: TestPoint; TestPoint_Pad_1.5x1.5mm
GND1: TestPoint; TestPoint_Pad_1.5x1.5mm
H1, H2: MountingHole_Pad; MountingHole_2.2mm_M2_ISO7380_Pad
J2: SBH11-PBPC-D05-ST-BK; CONN_SBH11-PBPC-D05-ST-BK_SUL
J4: SM04B-SRSS-TB; JST_SH_SM04B-SRSS-TB_1x04-1MP_P1.00mm_Horizontal
J6: Conn_01x02_Pin; PinHeader_1x02_P2.54mm_Vertical
J7: Conn_01x06_Socket; PinSocket_1x06_P2.54mm_Vertical
J8: S3B-PH-K-S; JST_PH_S3B-PH-K_1x03_P2.00mm_Horizontal
J9: 54-00284; TENSILITY_54-00284
J10: 1.25mm; CONN02_530470210_MOL
J11: DM3D-SF; HRS_DM3D-SF
Q1, Q2, Q4, Q5, Q6, Q7, Q8, Q9, Q10, Q12: G09P02L; TSOT-23
Q3, Q11: ISP12DP06NMXTSA1; PG-SOT223-4_INF
R1, R4, R5, R6, R19, R20, R21, R22, R23, R24, R25: 10K; R_1206_3216Metric_Pad1.30x1.75mm_HandSolder
R2, R14: 100K; R_1206_3216Metric_Pad1.30x1.75mm_HandSolder
R3, R9: 150K; R_1206_3216Metric_Pad1.30x1.75mm_HandSolder
R7, R8: 5.1K; R_1206_3216Metric_Pad1.30x1.75mm_HandSolder
R10, R13, R44, R45: 200K; R_1206_3216Metric_Pad1.30x1.75mm_HandSolder
R11, R12: NTCLE317E4103SBA; R_Axial_DIN0207_L6.3mm_D2.5mm_P10.16mm_Horizontal
R15: 100; R_1206_3216Metric_Pad1.30x1.75mm_HandSolder
R26: 20K; R_Axial_DIN0207_L6.3mm_D2.5mm_P10.16mm_Horizontal
R30, R31, R32, R33, R42: 205K; R_Axial_DIN0207_L6.3mm_D2.5mm_P10.16mm_Horizontal
R34, R35, R36, R37, R43: 301K; R_Axial_DIN0207_L6.3mm_D2.5mm_P10.16mm_Horizontal
R38: 3.6K; R_Axial_DIN0207_L6.3mm_D2.5mm_P10.16mm_Horizontal
R39: 22.1K; R_Axial_DIN0207_L6.3mm_D2.5mm_P10.16mm_Horizontal
R40: 71.5K; R_Axial_DIN0207_L6.3mm_D2.5mm_P10.16mm_Horizontal
R41: 402K; R_Axial_DIN0207_L6.3mm_D2.5mm_P10.16mm_Horizontal
RX1: TestPoint; TestPoint_Pad_1.5x1.5mm
Res1: Reset; SW_PUSH_6mm
SC1, SC2, SC3, SC4: Solar_Cell; C_Disc_D7.0mm_W2.5mm_P5.00mm
SOLA1: TestPoint; TestPoint_Pad_1.5x1.5mm
SOLB1: TestPoint; TestPoint_Pad_1.0x1.0mm
SW2: 1101M2S3AQE2; SPDT-1101M2_CNK
SW4: SA72SB0; R_Axial_DIN0207_L6.3mm_D2.5mm_P10.16mm_Horizontal
TX1: TestPoint; TestPoint_Pad_1.5x1.5mm
U1, U2, U3, U4: CDBA140SL-HF; CDBA-HF
U5: ESP32-WROOM-32E-N16; ESP32­WROOM­32E_EXP
U6: R_Array_SIP4
U9, U11: VS_10BQ015HM3_5BT; CR_SMBDO-214AA_VIS
U10: DW03C
U13, U15: MCP73833-xxx-UN; MSOP-10_3x3mm_P0.5mm
U14: MCP6234; PDIP14_300MC_MCH
U16: MCP6547T_I_MS; MSOP8_MC_MCH
U17: LM66100DCK; SOT-363_SC-70-6
U18: XC6210A332PR-G; SOT-89-5_Handsoldering
USB1: TestPoint; TestPoint_Pad_1.5x1.5mm

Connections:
/MicroSD/DAT1: J11.8 (DAT1), R21.2
/MicroSD/DAT2: J11.1 (DAT2), R22.2
/Power_And_Charging/Linear_Regulator/Vin: C17.1, Q10.1 (D), SW2.3 (A), U11.1, U18.4 (VIN)
/Power_And_Charging/MCP73833_Solar/Therm: R11.2, U13.8 (THERM)
/Power_And_Charging/MCP73833_Solar/Vbat: C12.1, Q5.1 (D), U13.9 (V_{BAT}), U13.10 (V_{BAT})
/Power_And_Charging/MCP73833_Solar/Vin: C11.1, Q4.1 (D), Q7.1 (D), SOLB1.1, U13.1 (V_{DD}), U13.2 (V_{DD})
/Power_And_Charging/MCP73833_USB/Therm: R12.2, U15.8 (THERM)
/Power_And_Charging/MCP73833_USB/Vbat: BAT1.1, C5.1, C15.1, J10.1, Q6.1 (D), Q9.1 (D), R15.1, U15.9 (V_{BAT}), U15.10 (V_{BAT})
/Power_And_Charging/Solar: Q11.3 (S), Q12.3 (S), R42.1, R44.1, SOLA1.1, U1.1, U2.1, U3.1, U4.1
/Power_And_Charging/UOVLO_Solar/Vout: Q3.3 (S), Q4.3 (S), Q12.1 (D)
/Power_And_Charging/Vbus_USB: C14.1, J2.1, J9.A9 (VBUS_A), J9.B9 (VBUS_B), Q5.2 (G), Q6.2 (G), Q7.2 (G), Q8.2 (G), R13.2, U9.2, U15.1 (V_{DD}), U15.2 (V_{DD}), USB1.1
/Solar_Measurement_Dual/Vin1: R30.1, SC1.1 (+), U1.2
/Solar_Measurement_Dual/Vin2: R31.1, SC2.1 (+), U2.2
/Solar_Measurement_Dual/Vin3: R32.1, SC3.1 (+), U3.2
/Solar_Measurement_Dual/Vin4: R33.1, SC4.1 (+), U4.2
Aout: J8.1, U5.10 (IO25)
Error: J2.4, U5.26 (IO4)
GND: Boot1.2, C1.2, C2.2, C3.1, C4.2, C9.2, C10.2, C11.2, C12.2, C13.1, C14.2, C15.2, C16.2, C17.2, C18.2, GND1.1, H1.1, H2.1, J2.9, J4.1, J7.1, J8.3, J9.A12 (GND_A), J9.B12 (GND_B), J11.6 (VSS), R2.1, R3.2, R4.1, R7.2, R8.2, R9.1, R10.2, R11.1, R12.1, R13.1, R14.2, R26.2, R34.1, R35.1, R36.1, R37.1, R38.2, R41.2, R43.2, R45.1, Res1.1, SC1.2 (-), SC2.2 (-), SC3.2 (-), SC4.2 (-), SW2.2 (C), U5.1 (GND), U5.15 (GND), U5.38 (GND), U5.39 (GND), U5.40 (GND), U5.41 (GND), U5.42 (GND), U5.43 (GND), U5.44 (GND), U5.45 (GND), U5.46 (GND), U5.47 (GND), U6.3 (GND), U10.3 (Vm), U13.5 (V_{SS}), U14.11 (V-), U15.5 (V_{SS}), U16.4 (V-), U18.2 (VSS)
unnamed: J6.2, J7.3
unnamed: J7.4, RX1.1, U5.34 (RXD0)
unnamed: J7.5, TX1.1, U5.35 (TXD0)
unnamed: J9.A5 (CC1), R7.1
unnamed: J9.B5 (CC2), R8.1
unnamed: J10.2, SW4.2
unnamed: Q1.1 (D), Q2.2 (G), R3.1
unnamed: Q3.1 (D), Q4.2 (G), R10.1
unnamed: Q5.3 (S), Q6.3 (S)
unnamed: Q7.3 (S), Q8.3 (S)
unnamed: Q8.1 (D), Q9.2 (G), Q10.2 (G), R14.1, U9.1, U11.2
unnamed: Q9.3 (S), Q10.3 (S)
unnamed: Q11.1 (D), Q12.2 (G), R45.2
unnamed: Q11.2 (G), R44.2, U16.1, U16.7
unnamed: SW2.1 (B), U18.1 (CE)
unnamed: C3.2, C4.1, R1.1, Res1.2, U5.3 (EN)
unnamed: Boot1.1, U5.25 (IO0)
unnamed: R4.2, U5.24 (IO2)
unnamed: J2.8, U5.14 (IO12)
unnamed: J2.7, U5.13 (IO14)
unnamed: J2.5, U5.11 (IO26)
unnamed: J2.6, U5.12 (IO27)
unnamed: C5.2, SW4.1, U10.2 (GND)
unnamed: R15.2, U10.1 (Vdd)
unnamed: R26.1, U13.6 (PROG)
unnamed: R30.2, R34.2, U14.3 (+)
unnamed: R31.2, R35.2, U14.5 (+)
unnamed: R32.2, R36.2, U14.10 (+)
unnamed: R33.2, R37.2, U14.12 (+)
unnamed: R38.1, U15.6 (PROG)
unnamed: R39.2, R40.1, U16.3 (+)
unnamed: R42.2, R43.1, U16.2 (-), U16.5 (+)
unnamed: R40.2, R41.1, U16.6 (-)
Periph_EN: Q1.2 (G), R2.2, U5.28 (IO17)
SCL: CLK1.1, J4.4, R6.2, U5.36 (IO22), U6.4 (SCL)
SDA: DAT1.1, J4.3, R5.2, U5.33 (IO21), U6.2 (SDA)
SPI_CLK: J11.5 (CLK), R19.2, U5.30 (IO18)
SPI_MISO: J11.7 (DAT0), R20.2, U5.31 (IO19)
SPI_MOSI: J11.3 (CMD), R24.2, U5.37 (IO23)
STAT1: J2.2, U15.3 (STAT1)
STAT2: J2.3, U15.4 (STAT2)
Solar_Chg_EN: Q3.2 (G), R9.2, U5.16 (IO13)
V_Solar1: U5.8 (IO32), U14.1, U14.2 (-)
V_Solar2: U5.6 (IO34), U14.6 (-), U14.7
V_Solar3: U5.7 (IO35), U14.8, U14.9 (-)
V_Solar4: U5.9 (IO33), U14.13 (-), U14.14
Vbus: Bus1.1, C1.1, C2.1, C16.1, C18.1, J6.1, Q1.3 (S), Q2.3 (S), R1.2, R39.1, U5.2 (3V3), U16.8 (V+), U18.5 (VOUT)
Vperiph: C9.1, C10.1, C13.2, J4.2, J8.2, J11.4 (VDD), Q2.1 (D), R5.1, R6.1, R19.1, R20.1, R21.1, R22.1, R23.1, R24.1, R25.2, U6.1 (VDD), U14.4 (V+)
uSD_CS: J11.2 (CD/DAT3), R23.2, U5.29 (IO5)
uSD_DET: J11.SW-A, R25.1, U5.27 (IO16)

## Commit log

2025-11-18 Fall 2025 Code
2025-11-24 Added empty file system
    Added a zip folder containing an empty, unmodified version of the filesystem used in the Fall 2025 prototype.
2025-11-24 Updated EmptyFS.zip
    Zip file was updated to remove an unnecessary container folder.
2025-11-24 Update README.md
    Formatting changes
2026-01-20 Added Spring 2026 folder with Kicad subfolder
2026-01-20 charging circuit
    1/20/2026
2026-01-24 Sketch work
    1/24/2026 added stuff from last semester and changes the liniear regulator to handle more than 200 mA of current because the esp does a radio check on startup that is >200 mA for the wifi capabilitie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
2026-01-24 Weird
    Git hub being funny
2026-01-24 Sketch work 2
    General cleanup and adding a few more components that don't require much brainpower
2026-01-30 Added Charging Schematic
2026-01-30 Sensor Fun
    Had to annotate in order to assign footprints, If that messed anything up I'd be happy to fix it. Added a basic 1x4 header for the temp sensor and added the correct female pins/header footprint for t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
2026-01-31 Updated Charging Circuit
    Replaced TP4056 with MCP73833, replaced schottky diodes
2026-01-31 Added ESP32 micro and mostly completed its wiring to peripherals
2026-01-31 minor microcontroller adjustments
2026-02-01 Updates to power schematic
    Replaced certain selection transistors for lower Rds_on, added thermal cutoff and DW03 for battery protection, swapped in 4-channel op-amps for solar measurement, various misc. improvements.
2026-02-02 Schematic updates
    Added USB charge LEDs, updated PMOS gates, added micro connections and revised some of the charging set up.
2026-02-02 Minor updates to charge/power
2026-02-02 Footprint correction
    Changed the DHT20 from a header pin to the recommended SIP. Also had to reannotate in order to assign footprints.
2026-02-03 Charging updates and MicroSD started
2026-02-03 Micro-SD subsheet
2026-02-03 Fixed USB-C and Linear Regulator Sheetfiles
2026-02-03 Misc. Charging Changes
2026-02-04 Fixed solar measurement circuit
2026-02-04 Added power switching
2026-02-04 Found NTC Thermistor
2026-02-06 StripBoardAddon
    Instead of making a whole different sketch I used a hierarch so the pins match with the ones on the esp32. It's got the 4 pushbuttons and 3 LED's. I could not find where the LED's are supposed to be 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
2026-02-06 StripBoardTouchUp
    Made everything on the stripboard go into connector pins that then integrate into the main sketch. Made Error LED go into pin 26 on the esp32.
2026-02-07 Misc. changes
    Updated peripheral power switch, UI board connections
2026-02-07 Misc. fixes to schematic
2026-02-08 Footprint updates
    Misc. schematic fixes, mostly updated/added footprints where needed.
2026-02-08 Programming ports on schematic
2026-02-09 Started PCB
2026-02-09 Rough PCB Layout
2026-02-10 Sanity check
    Added 0.1uF caps to the MCP in the UOVLO solar and the Solar measurement pages. also Vmeas1 was not connected the the op amp in the Solar measurement.
2026-02-10 Resub from last
    I forgot to save some of my changes from my last push
2026-02-10 Refined PCB layout
2026-02-10 Began PCB routing
    Routed solar input, measurement and protections
2026-02-10 Re-routed to fix issue on schematic
2026-02-11 PCB Routing
    I believe this to be the product of mania, but it may yet function.
2026-02-11 Charge circuit essentially added to pcb
2026-02-12 Re-routed to free trapped lines
    Repositioned & re-routed to free some nets and get parts within board edge (sorry Noah)
2026-02-12 Nearly finished routing
    uSD and two I2C connectors remaining.
2026-02-12 PCB almost finalized
    few ground planes left to connect but components are fully connected outside those grounds.
2026-02-12 Onshape folder and start
    started a rough outline of our housing. cant save like kicad so let me know if you can't import the files
2026-02-12 PCB Pre-Check complete
2026-02-13 Housing refining
    Refined the housing a bit and added a lid. Can discuss ways to enclose and stay enclosed at meetings, such as slide on lids or magnets or screws. this is just a good base.
2026-02-13 Routing adjustments
    Adjusted some lines to improve positions of connectors & uSD. Ground plane needs to be re-added after the top-right corner is improved.
2026-02-13 Further PCB Improvements
    Finally fixed STAT1 STAT2 running along bottom of board.
2026-02-14 PCB Adjustments
    Placed Mounting holes and attributions, cleaned up some traces. Still needs ground plane behind.
2026-02-14 PCB Finishing Steps
    Added additional details on silkscreen, added ground plane, misc. touchups
2026-02-15 Screw holes for Housing
    Added holes for possible screws, based off of m3x16 socket head cap screw, link is in general parts research. also added possible ventilation
2026-02-16 Finalizing checks/tweaks to PCB
    Fixed a few footprint mask and silkscreen issues
2026-02-18 Quick clearance adjustment on PCB
2026-02-18 Generated Gerber/Drill files
2026-03-07 New plant selection method
    Much tweaking/testing needed, but the base functionality is there (if a bit ugly).
2026-03-08 Small fixes/improvement to code
2026-03-12 Primarily UI improvements
    Added bitmaps for "stand-in" symbols, prettied up some menus, started on new recommendation system.
2026-03-12 Housing First Draft
    Made a rough first draft to base our housing on. mostly just the base structure and holes for the SD card, moisture sensor and solar panels.
2026-03-12 creating local project repo
2026-03-12 file management
2026-03-13 UI Improvements
    Continued refining UI
2026-03-17 Added JHA PDF
    WHAAAAAA
2026-03-17 JHA with shane sig
2026-03-18 added sensor averages
    using the active plant from the saver files
2026-03-19 Uploaded working Parser Script
    using API keys from drive script will pull all plants and format data for use with other code
2026-03-20 Merged local UI improvements with current codebase
2026-03-20 adding webapp frontend
2026-03-20 Updates after testing with larger database
2026-03-20 added range/single value handling for local UI plant selections being updated on the webapp
2026-03-23 Misc. changes to code of varying but wholly underwhelming importance to national security.
2026-03-24 adding more robust error handling for SD initialization
2026-03-24 error handling for webapp and most average -> key conversions (except humidity)
2026-03-25 Updated water/light mappings
2026-03-25 updated water thresholds
2026-03-26 Fixed a few minor UI issues.
2026-03-28 updating thresholds, frontend for recommendations
2026-03-28 Finished Recommendations, UI updates
2026-03-28 Added in holder for web recommended plants
2026-03-29 webapp recommendations finished
2026-03-29 changing autocomplete search method
2026-03-29 fix attempt #2, large scale webapp
2026-03-29 more webapp fixes
2026-03-29 Fixed catnip Problem
    was deleting the "water requirement" object in "data" instead of deleting the whole plant
    indent also removed
2026-03-29 overhaul of webapp database access
2026-03-30 Ready for RID (pRinted cIrcuit boaRd)
2026-03-30 Returned last ID to correct value
2026-04-03 Made Kicad V2, Started on fixes
2026-04-16 Organized Repo
2026-04-20 Minor cleanup, slight tweaks in V2
2026-04-20 Added Onshape STL files
2026-04-22 Added assets for readme
